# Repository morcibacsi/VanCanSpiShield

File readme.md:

# VAN CAN SPI Shield

### What is it ?
This is an SPI "shield" designed for my [PSA VAN-CAN protocol bridge hardware][psavancanbridgehw].

On one side, it has an MCP2515 CAN bus controller, and on the other side, it has a TSS463C VAN bus controller. Both sides contain all the necessary components. Obviously only one side can be used at a time. 

The files are created with KiCad. 

The main branch contains only this readme file as there might be multiple revisions and having a continuous history does not really make sense. 
So every revision will have its own branch. They will be in the state as I sent them to the manufacturing company.

### Available revisions

- [Rev 1.0][version_10]
- [Rev 1.1][version_11]

[psavancanbridgehw]: https://github.com/morcibacsi/PSAVanCanBridgeHW
[version_10]: https://github.com/morcibacsi/VanCanSpiShield/tree/v1.0
[version_11]: https://github.com/morcibacsi/VanCanSpiShield/tree/v1.1

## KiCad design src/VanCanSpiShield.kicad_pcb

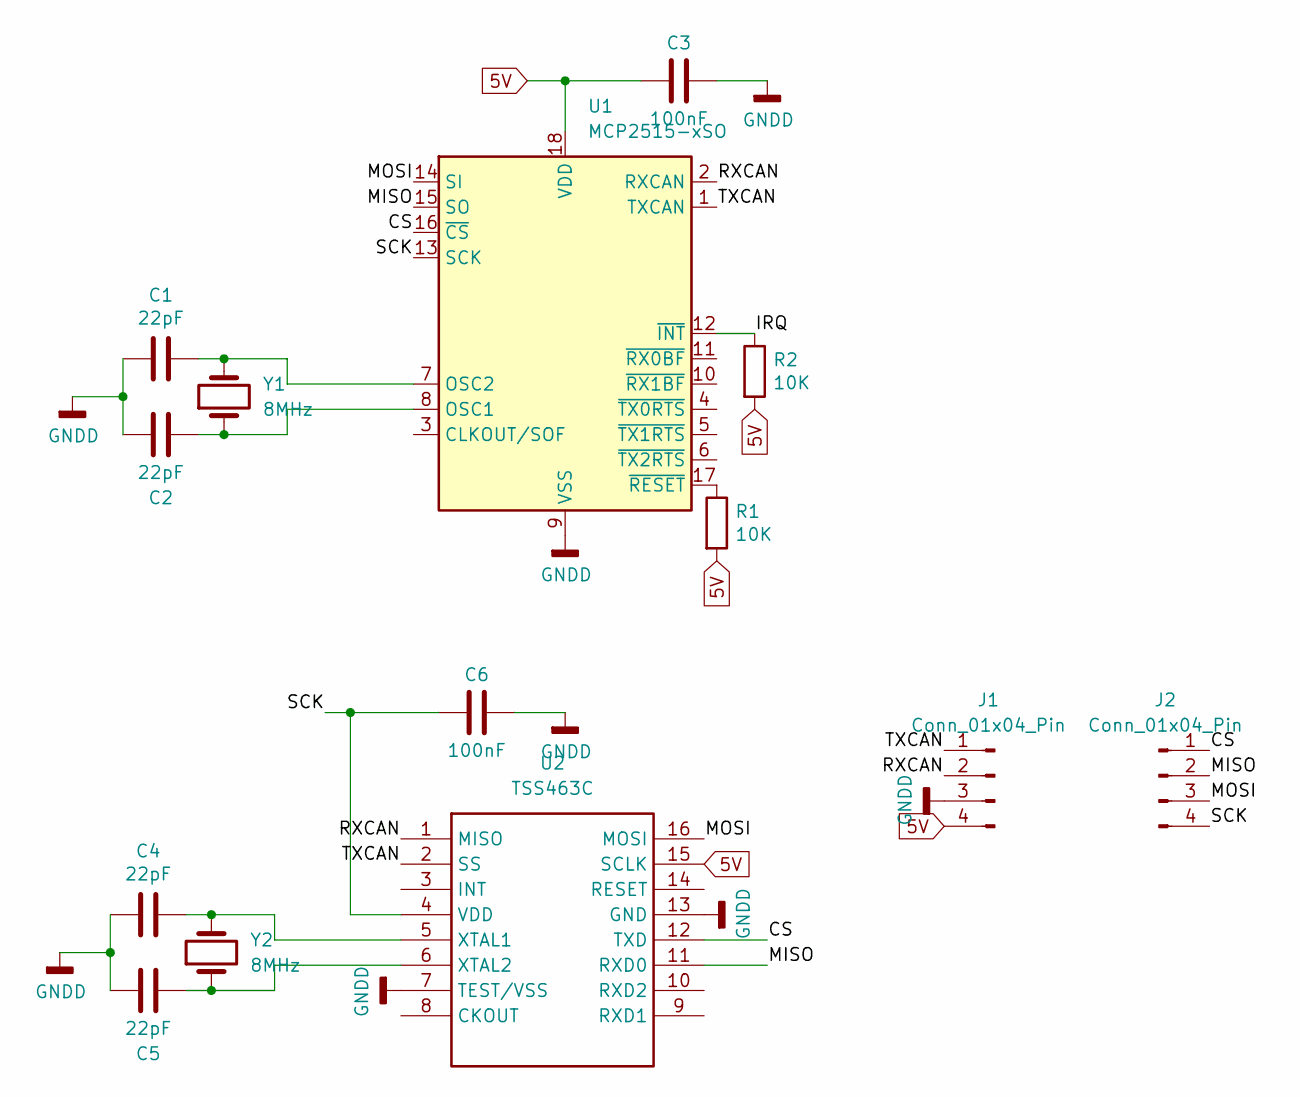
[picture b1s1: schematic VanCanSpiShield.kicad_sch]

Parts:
C1, C2, C4, C5: 22pF; C_0603_1608Metric_Pad1.08x0.95mm_HandSolder; LCSC C1653
C3, C6: 100nF; C_0603_1608Metric_Pad1.08x0.95mm_HandSolder; LCSC C14663
J1, J2: Conn_01x04_Pin; PinHeader_1x04_P2.54mm_Vertical
R1, R2: 10K; R_0603_1608Metric_Pad0.98x0.95mm_HandSolder; LCSC C25804
U1: MCP2515-xSO; SOIC-18W_7.5x11.6mm_P1.27mm; LCSC C12368
U2: TSS463C; SO16L
Y1, Y2: 8MHz; Crystal_SMD_5032-2Pin_5.0x3.2mm; LCSC C115962

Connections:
5V: C3.2, J1.4, R1.2, R2.2, U1.18 (VDD), U2.15 (SCLK)
/CS: J2.1, U1.16 (~CS), U2.12 (TXD)
/IRQ: R2.1, U1.12 (~INT)
/MISO: J2.2, U1.15 (SO), U2.11 (RXD0)
/MOSI: J2.3, U1.14 (SI), U2.16 (MOSI)
/RXCAN: J1.2, U1.2 (RXCAN), U2.1 (MISO)
/SCK: C6.2, J2.4, U1.13 (SCK), U2.4 (VDD)
/TXCAN: J1.1, U1.1 (TXCAN), U2.2 (SS)
GNDD: C1.2, C2.2, C3.1, C4.2, C5.2, C6.1, J1.3, U1.9 (VSS), U2.7 (TEST/VSS), U2.13 (GND)
unnamed: C2.1, U1.8 (OSC1), Y1.1
unnamed: C1.1, U1.7 (OSC2), Y1.2
unnamed: R1.1, U1.17 (~RESET)
unnamed: C4.1, U2.5 (XTAL1), Y2.2
unnamed: C5.1, U2.6 (XTAL2), Y2.1

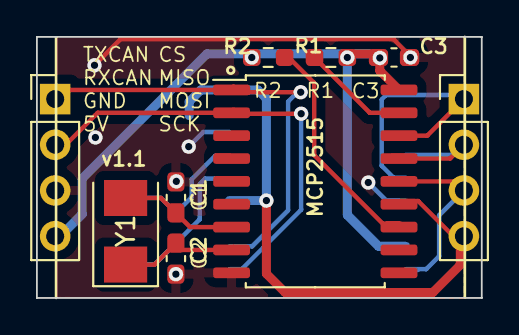
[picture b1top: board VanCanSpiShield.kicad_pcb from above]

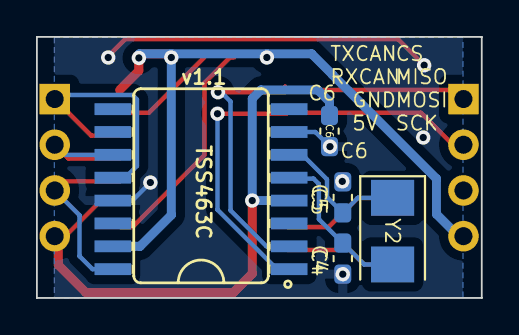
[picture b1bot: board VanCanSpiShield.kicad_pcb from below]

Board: 2 copper layers, 24.7 x 14.5 mm, 14 parts (5 on the bottom side), 14 nets.

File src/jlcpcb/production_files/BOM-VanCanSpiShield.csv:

Comment,Designator,Footprint,LCSC,Quantity
8MHz,"Y1,Y2",Crystal_SMD_5032-2Pin_5.0x3.2mm,C115962,2
MCP2515-xSO,U1,SOIC-18W_7.5x11.6mm_P1.27mm,C12368,1
100nF,"C3,C6",C_0603_1608Metric_Pad1.08x0.95mm_HandSolder,C14663,2
22pF,"C1,C2,C4,C5",C_0603_1608Metric_Pad1.08x0.95mm_HandSolder,C1653,4
10K,"R1,R2",R_0603_1608Metric_Pad0.98x0.95mm_HandSolder,C25804,2
TSS463C,U2,SO16L,,1
Conn_01x04_Pin,J1,PinHeader_1x04_P2.54mm_Vertical,,1
Conn_01x04_Pin,J2,PinHeader_1x04_P2.54mm_Vertical,,1

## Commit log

2024-11-11 Added gitignore
2024-11-11 Added readme.md
2024-11-11 Added files
2025-03-28 Updated readme regarding TSS463C issue
